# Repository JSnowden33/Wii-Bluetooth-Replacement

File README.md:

# Wii Bluetooth Replacement

This project is a full replacement for the Nintendo Wii's Bluetooth module. Emulation of the Bluetooth module is performed on the PIC32 based on [rnconrad's emulator](https://github.com/rnconrad/WiiBluetoothEmulator), while controller connectivity on the ESP32 is based on [btstack](https://github.com/bluekitchen/btstack).

The device interfaces with various wireless controllers and emulates up to 4 virtual Wii Remotes to communicate with the Wii. Virtual Wii Remotes can be configured to have a Nunchuk, Classic Controller, or neither. Currently supported controllers are Wii Remote, Wii U Pro Controller, Joy-Con, and Switch Pro Controller. Joy-Con can also be used through wired functionality.

The PCB for this design can be purchased [here](https://oshpark.com/shared_projects/co8uBM0Z).

## Usage

The board needs to be powered by 3.3V. The only connection needed to the Wii are the D+ and D- USB lines, which should be wired where the Bluetooth module normally sits. The 5V input is only used for Joy-Con charging and not needed to use the Joy-Con. The "S" pin is for the sync button, which can be a normally open tact switch connected to GND.

## Supported Features

- Permanent syncing: Press the sync button on the ESP32 along with the sync button on any controllers you want to pair. The ESP32 will pair and store each controller's information so reconnection works smoothly. Joy-Con can also be paired by docking them to the ESP32.

- Extension switching: Controllers that don't support physical extensions (Nunchuk and Classic Controller) can cycle through virtual extensions. Long-press Home to cycle through each one. Switch and Wii U Pro Controllers support sideways Wii Remote, Nunchuk, and Classic Controller. Dual Joy-Con support Nunchuk and Classic Controller. Single Joy-Con (R) supports only vertical Wii Remote and Joy-Con (L) supports only Nunchuk.

- IR pointer emulation: The Wii Remote IR pointer is emulated by gyro control (for Joy-Con, Switch Pro, and Wii Remote Plus) or by the right joystick for any controllers that have it. The cursor can be re-centered by pressing R (long-press Plus on Wii Remote). Gyro can be re-calibrated by long-pressing R (long-press Home on Wii Remote) and letting the controller be still for a few seconds.

## Planned Features

- New platform: A hardware revision is planned based on the PIC32MX470F512 and the TI CC2564 BT module. This will hopefully resolve some current hardware issues and improve data throughput with more processing speed.

- DPad to joystick mapping: The Wii Remote DPad will eventually be mapped to the left joystick whenever a controller has no virtual extension attached.

- More single Joy-Con functionality: Each single Joy-Con (L or R) will eventually be usable as its own Wii Remote. Single Joy-Con mode will be enabled by holding SL + SR for a few seconds after the Joy-Con is connected. Each will function as a sideways Wii Remote with full motion control and a gyro pointer which can be toggled by pressing the joystick.

- More wired Joy-Con functionality: Wired Joy-Con are not well tested and implementation is unfinished. They currently do not support virtual extensions or rumble. 

- Wii Motion Plus: Motion Plus emulation is mostly implemented but not tested. It should be functional on any controller with a gyroscope.

## Known Issues

This project is experimental and has plenty of bugs. Below is a list of some important issues that still need fixing.

- Wii Remote connectivity: Currently only newer Wii Remotes (TR versions) can auto-connect to the ESP32 by pressing any button on the controller. Older Wii Remotes must be synced every time. This is due to a hardware incompatibility with the ESP32 and fixing it will require moving away from the ESP32 platform.

- Joy-Con connectivity: Joy-Con are finnicky and sometimes won't auto-connect. Fixing this will also require moving away from the ESP32 platform (but this issue seems to exist on some other platforms too). Resetting the Joy-Con by pressing the black button on the side seems to help.

- Reconnecting a controller: The PIC32 currently doesn't handle reconnections very well and may become unusable in-game if you disconnect a controller and try to reconnect it. Power cycling may be necessary (pressing the reset button on the Wii doesn't reinitialize the Bluetooth module).

- Multiplayer use: Connecting more players beyond player 1 may not work well or at all depending on the software. Using two Joy-Con for the same player works fine.

- HD rumble: Joy-Con and Switch Pro Controllers do support rumble and it usually works fine, but sometimes it will stop working until the controller is reconnected. Needs to be looked into.

## Joy-Con Wiring

The Joy-Con wired connection follows the pin numbering provided [here](https://github.com/dekuNukem/Nintendo_Switch_Reverse_Engineering). On each Joy-Con, the pin names vs. pin numbers are as follows:

- 5V: Pin 4
- TX: Pin 5
- FC1: Pin 6
- GND: Pin 7
- RX: Pin 8
- FC2: Pin 10

If a Joy-Con rail connector is wired to the board, pins 1, 2, 3, and 7 on the rail should be grounded. Pin 9 should be left unconnected. Connecting 5V to pin 4 for charging is optional. Note that having 5V active on the rail at all times may be unsafe if the connection isn't tight. 
When assembling the board, components U1, U2, C3, C4, and C6 are used only for Joy-Con connectivity and can be left off if wired Joy-Con will not be used.

## Compiling and Programming

### PIC32

Compiling the PIC32 software requires MPLAB X IDE with XC32 installed. Simply open the .X folder under Software/PIC32 as an MPLAB project and compile. The compiled image can be flashed using a PICKit3 connected to the MCLR, PGD, and PGC pins on the underside of the board. The board will need to be powered externally and the PICKit3 will need to be connected to 3.3V and GND references.

### ESP32

Compiling the ESP32 software requires installing both esp-idf and btstack. On Windows 10, I use the Msys32 terminal for esp-idf. Btstack can be downloaded from [here](https://github.com/bluekitchen/btstack). The port/esp32/integrate_btstack.py script will install btstack to your system after esp-idf has been installed. The software can be flashed to the ESP32 using any USB-serial programmer that has the appropriate transistors on the DTS and RTS lines. Those transistors should be connected to the EN and BOOT pins on the underside of the board (RX and TX go to the communication pins of the serial port). Running "make flash" in the Msys32 terminal will compile and flash the software to your board. The first compilation will take a VERY long time.

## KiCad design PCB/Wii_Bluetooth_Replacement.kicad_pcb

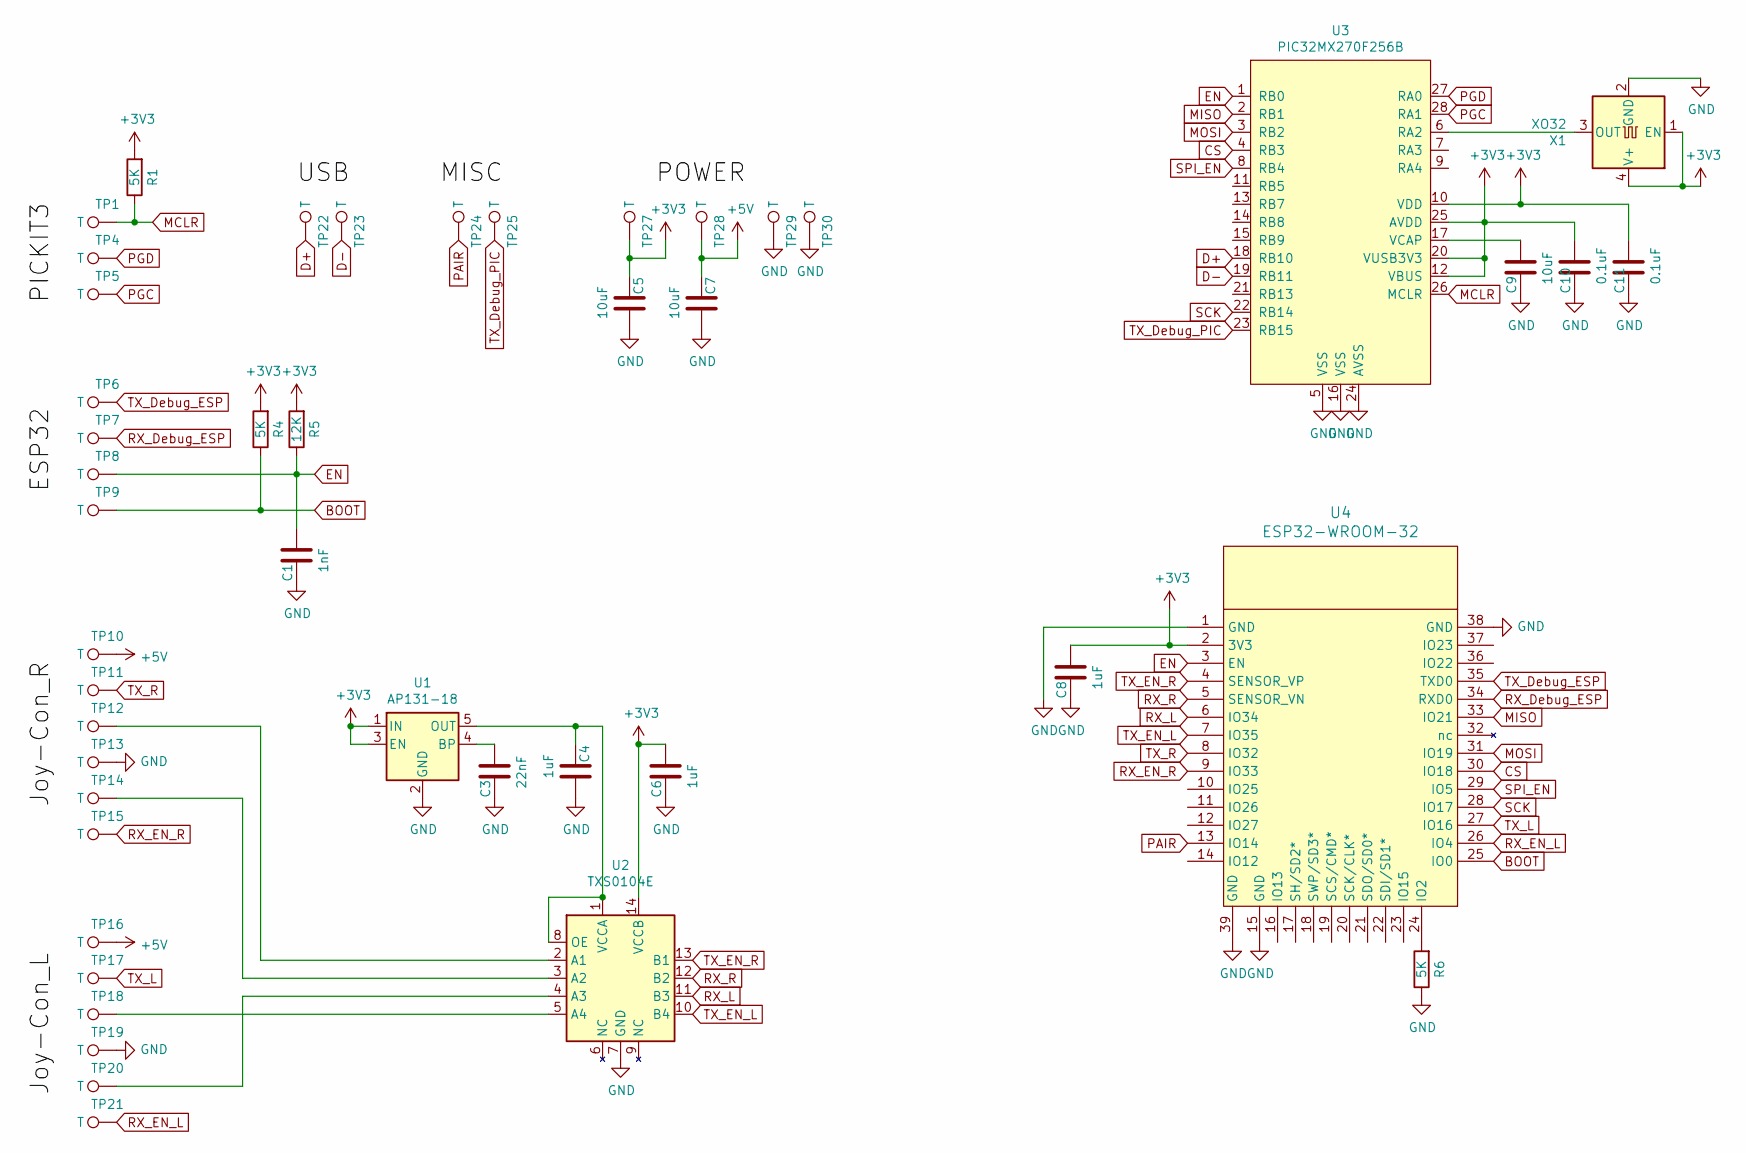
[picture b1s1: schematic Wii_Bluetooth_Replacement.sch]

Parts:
C1: 1nF; C_0603_1608Metric
C3: 22nF; C_0603_1608Metric
C4, C6, C8: 1uF; C_0603_1608Metric
C5, C7, C9: 10uF; C_1206_3216Metric
C10, C11: 0.1uF; C_0603_1608Metric
R1, R4, R6: 5K; R_0603_1608Metric
R5: 12K; R_0603_1608Metric
TP1, TP4, TP5, TP6, TP7, TP8, TP9, TP10, TP11, TP12, TP13, TP14, TP15, TP16, TP17, TP18, TP19, TP20, TP21, TP22, TP23, TP24, TP25: T; TestPoint_Pad_D0.7mm_NoSilk
TP27, TP28, TP29, TP30: T; TestPoint_Pad_D1.0mm_NoSilk
U1: AP131-18; SOT-23-5
U2: TXS0104E; VQFN-14_3.5x3.5mm_P0.5mm
U3: PIC32MX270F256B; QFN-28-1EP_6x6mm_P0.65mm_EP2.5x2.5mm
U4: ESP32-WROOM-32
X1: XO32; Oscillator_SMD_EuroQuartz_XO32-4Pin_3.2x2.5mm

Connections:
+3V3: C5.2, C6.1, C8.1, C10.1, C11.1, R1.2, R4.2, R5.2, TP27.1, U1.1 (IN), U1.3 (EN), U2.14 (VCCB), U3.10 (VDD), U3.12 (VBUS), U3.20 (VUSB3V3), U3.25 (AVDD), U4.2 (3V3), X1.1 (EN), X1.4 (V+)
+5V: C7.2, TP10.1, TP16.1, TP28.1
BOOT: R4.1, TP9.1, U4.25 (IO0)
CS: U3.4 (RB3), U4.30 (IO18)
D+: TP22.1, U3.18 (RB10)
D-: TP23.1, U3.19 (RB11)
EN: C1.1, R5.1, TP8.1, U3.1 (RB0), U4.3 (EN)
GND: C1.2, C3.2, C4.1, C5.1, C6.2, C7.1, C8.2, C9.2, C10.2, C11.2, R6.1, TP13.1, TP19.1, TP29.1, TP30.1, U1.2 (GND), U2.7 (GND), U2.15, U3.5 (VSS), U3.16 (VSS), U3.24 (AVSS), U3.29, U4.1 (GND), U4.15 (GND), U4.38 (GND), U4.39 (GND), X1.2 (GND)
MCLR: R1.1, TP1.1, U3.26 (MCLR)
MISO: U3.2 (RB1), U4.33 (IO21)
MOSI: U3.3 (RB2), U4.31 (IO19)
unnamed: C3.1, U1.4 (BP)
unnamed: C4.2, U1.5 (OUT), U2.1 (VCCA), U2.8 (OE)
unnamed: C9.1, U3.17 (VCAP)
unnamed: R6.2, U4.24 (IO2)
unnamed: TP12.1, U2.2 (A1)
unnamed: TP14.1, U2.3 (A2)
unnamed: TP18.1, U2.5 (A4)
unnamed: TP20.1, U2.4 (A3)
unnamed: U3.6 (RA2), X1.3 (OUT)
PAIR: TP24.1, U4.13 (IO14)
PGC: TP5.1, U3.28 (RA1)
PGD: TP4.1, U3.27 (RA0)
RX_Debug_ESP: TP7.1, U4.34 (RXD0)
RX_EN_L: TP21.1, U4.26 (IO4)
RX_EN_R: TP15.1, U4.9 (IO33)
RX_L: U2.11 (B3), U4.6 (IO34)
RX_R: U2.12 (B2), U4.5 (SENSOR_VN)
SCK: U3.22 (RB14), U4.28 (IO17)
SPI_EN: U3.8 (RB4), U4.29 (IO5)
TX_Debug_ESP: TP6.1, U4.35 (TXD0)
TX_Debug_PIC: TP25.1, U3.23 (RB15)
TX_EN_L: U2.10 (B4), U4.7 (IO35)
TX_EN_R: U2.13 (B1), U4.4 (SENSOR_VP)
TX_L: TP17.1, U4.27 (IO16)
TX_R: TP11.1, U4.8 (IO32)

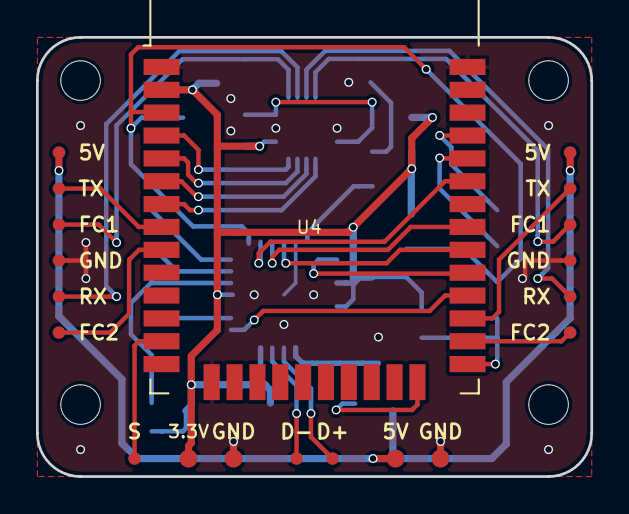
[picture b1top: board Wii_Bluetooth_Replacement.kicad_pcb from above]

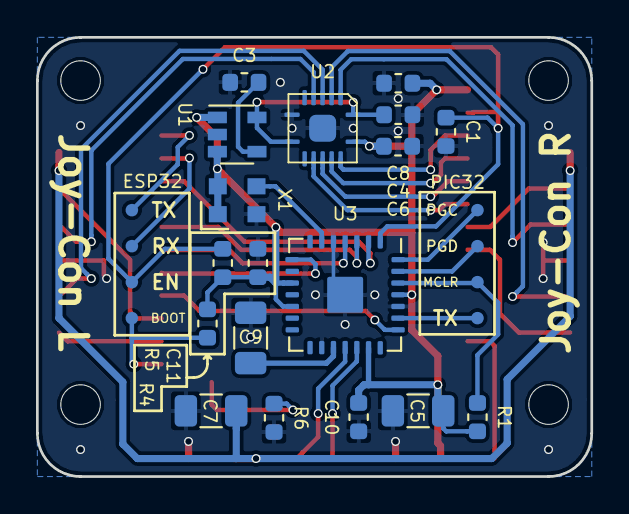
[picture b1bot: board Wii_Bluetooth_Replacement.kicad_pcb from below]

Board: 2 copper layers, 30.8 x 24.4 mm, 46 parts (26 on the bottom side), 36 nets.

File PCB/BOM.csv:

Qty,Description,Value,Link
1,SMD Capacitor 0603,1nF,Any - should be at least 6.3V tolerant
1,SMD Capacitor 0603,22nF,Any - should be at least 6.3V tolerant
2,SMD Capacitor 0603,0.1uF,Any - should be at least 6.3V tolerant
3,SMD Capacitor 0603,1uF,Any - should be at least 6.3V tolerant
3,SMD Capacitor 1206,10uF,Any - should be at least 6.3V tolerant
3,SMD Resistor 0603,5kOhm,Any
1,SMD Resistor 0603,12kOhm,Any
1,1.8V Linear Regulator,RT9193-18GB,https://www.digikey.com/product-detail/en/richtek-usa-inc/RT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
1,Logic Level Translator,TXS0104ERGYR,https://www.digikey.com/product-detail/en/texas-instruments/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
1,PIC32 Microcontroller,PIC32MX270F256B-50I/ML,https://www.digikey.com/product-detail/en/microchip-technolo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
1,ESP32 Microcontroller,ESP32-WROOM-32D,https://www.digikey.com/product-detail/en/espressif-systems/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
1,8MHz Oscillator,ASEM1-8.000MHZ-LC-T,https://www.digikey.com/product-detail/en/abracon-llc/ASEM1-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

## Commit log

2019-08-23 Initial upload
2019-08-23 Add image
2019-08-23 Added image
